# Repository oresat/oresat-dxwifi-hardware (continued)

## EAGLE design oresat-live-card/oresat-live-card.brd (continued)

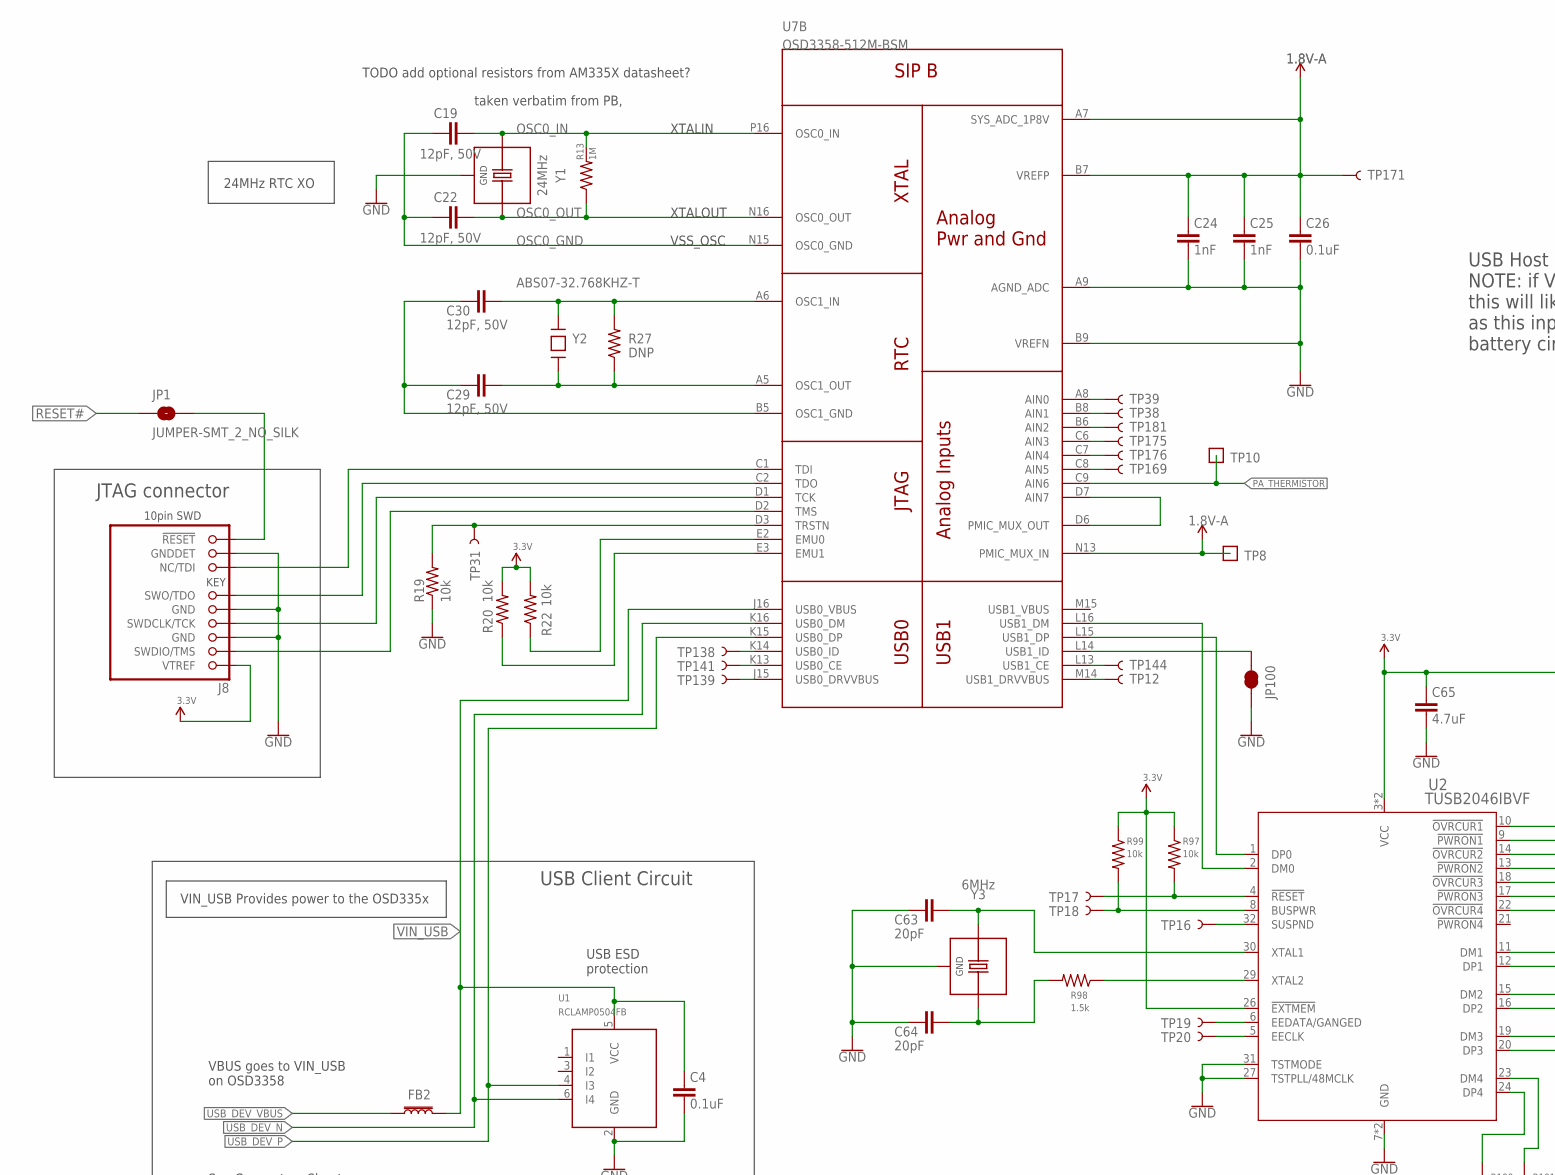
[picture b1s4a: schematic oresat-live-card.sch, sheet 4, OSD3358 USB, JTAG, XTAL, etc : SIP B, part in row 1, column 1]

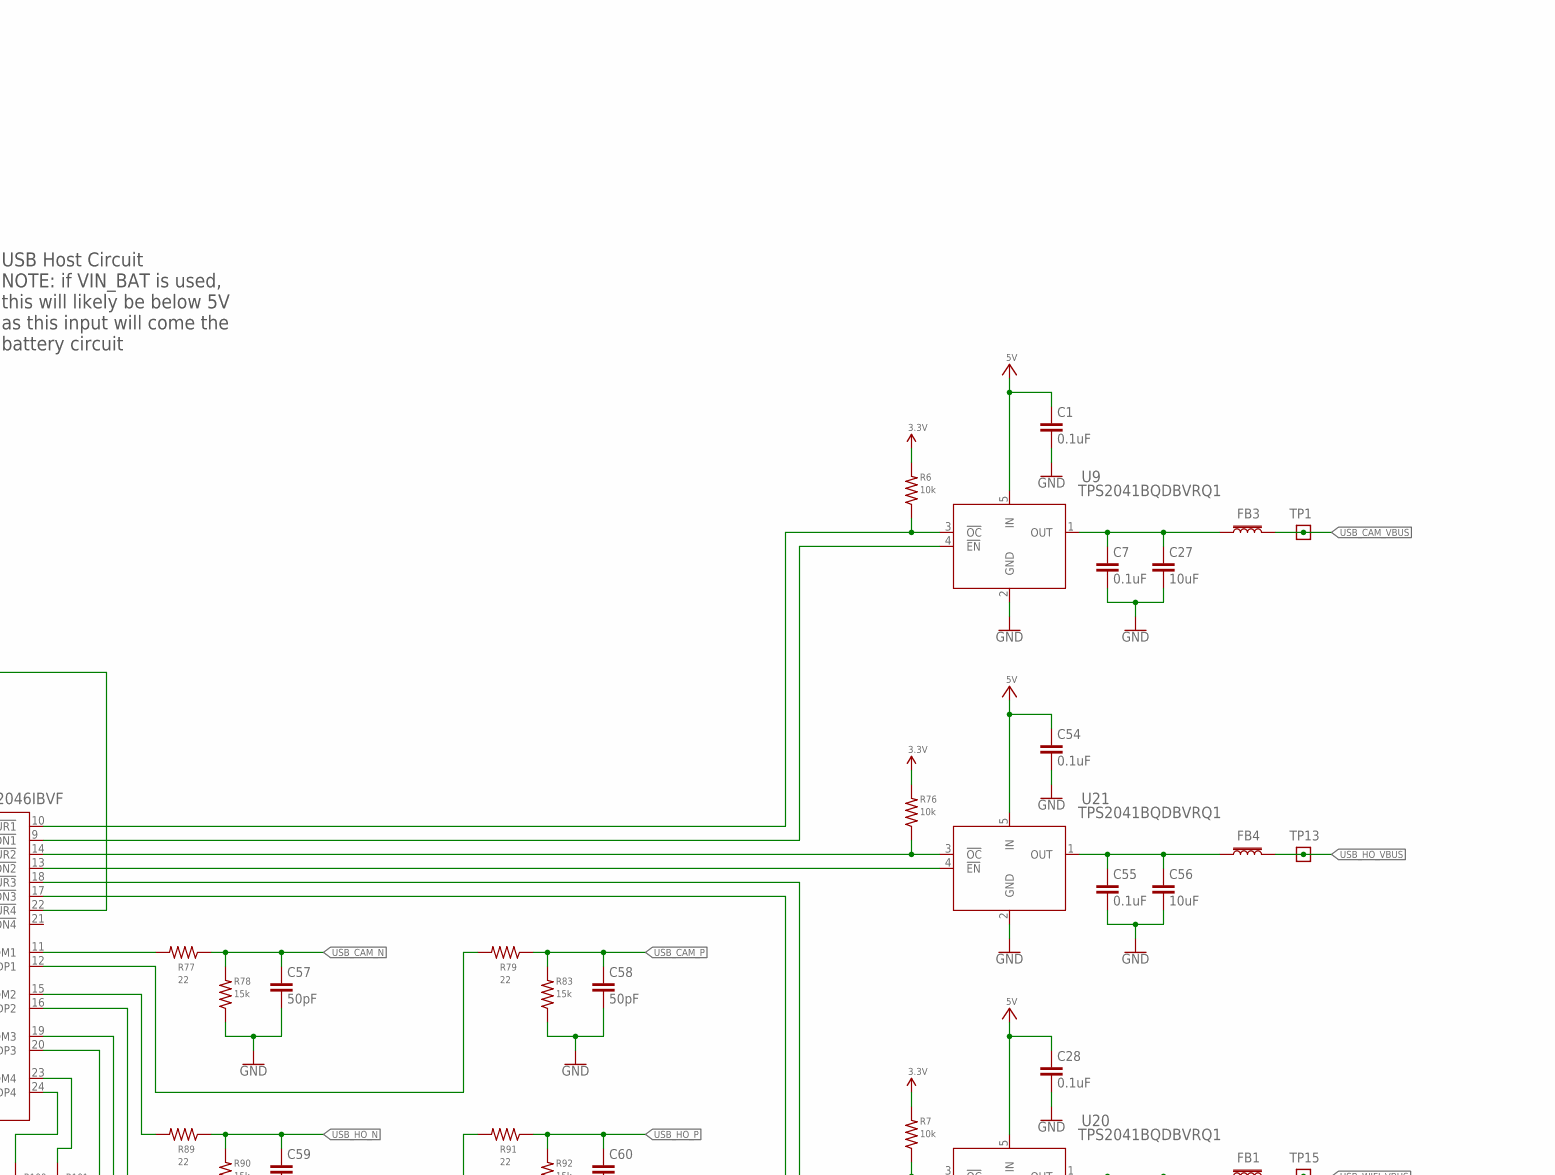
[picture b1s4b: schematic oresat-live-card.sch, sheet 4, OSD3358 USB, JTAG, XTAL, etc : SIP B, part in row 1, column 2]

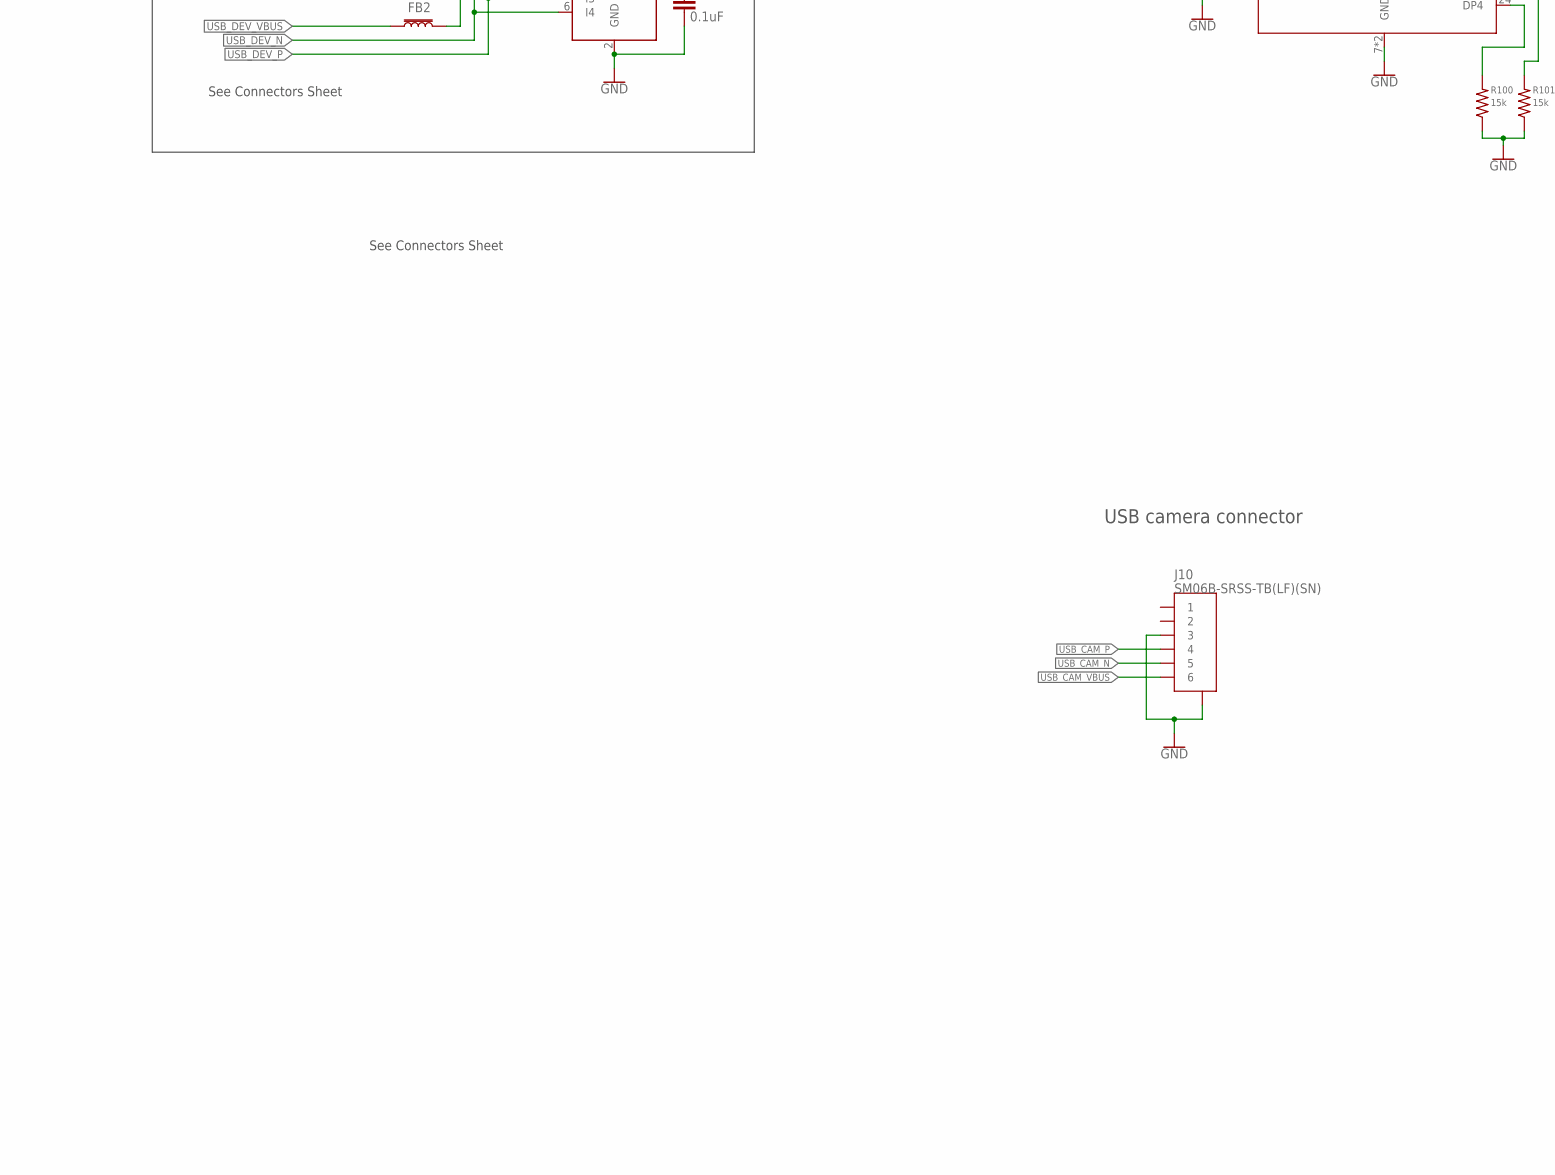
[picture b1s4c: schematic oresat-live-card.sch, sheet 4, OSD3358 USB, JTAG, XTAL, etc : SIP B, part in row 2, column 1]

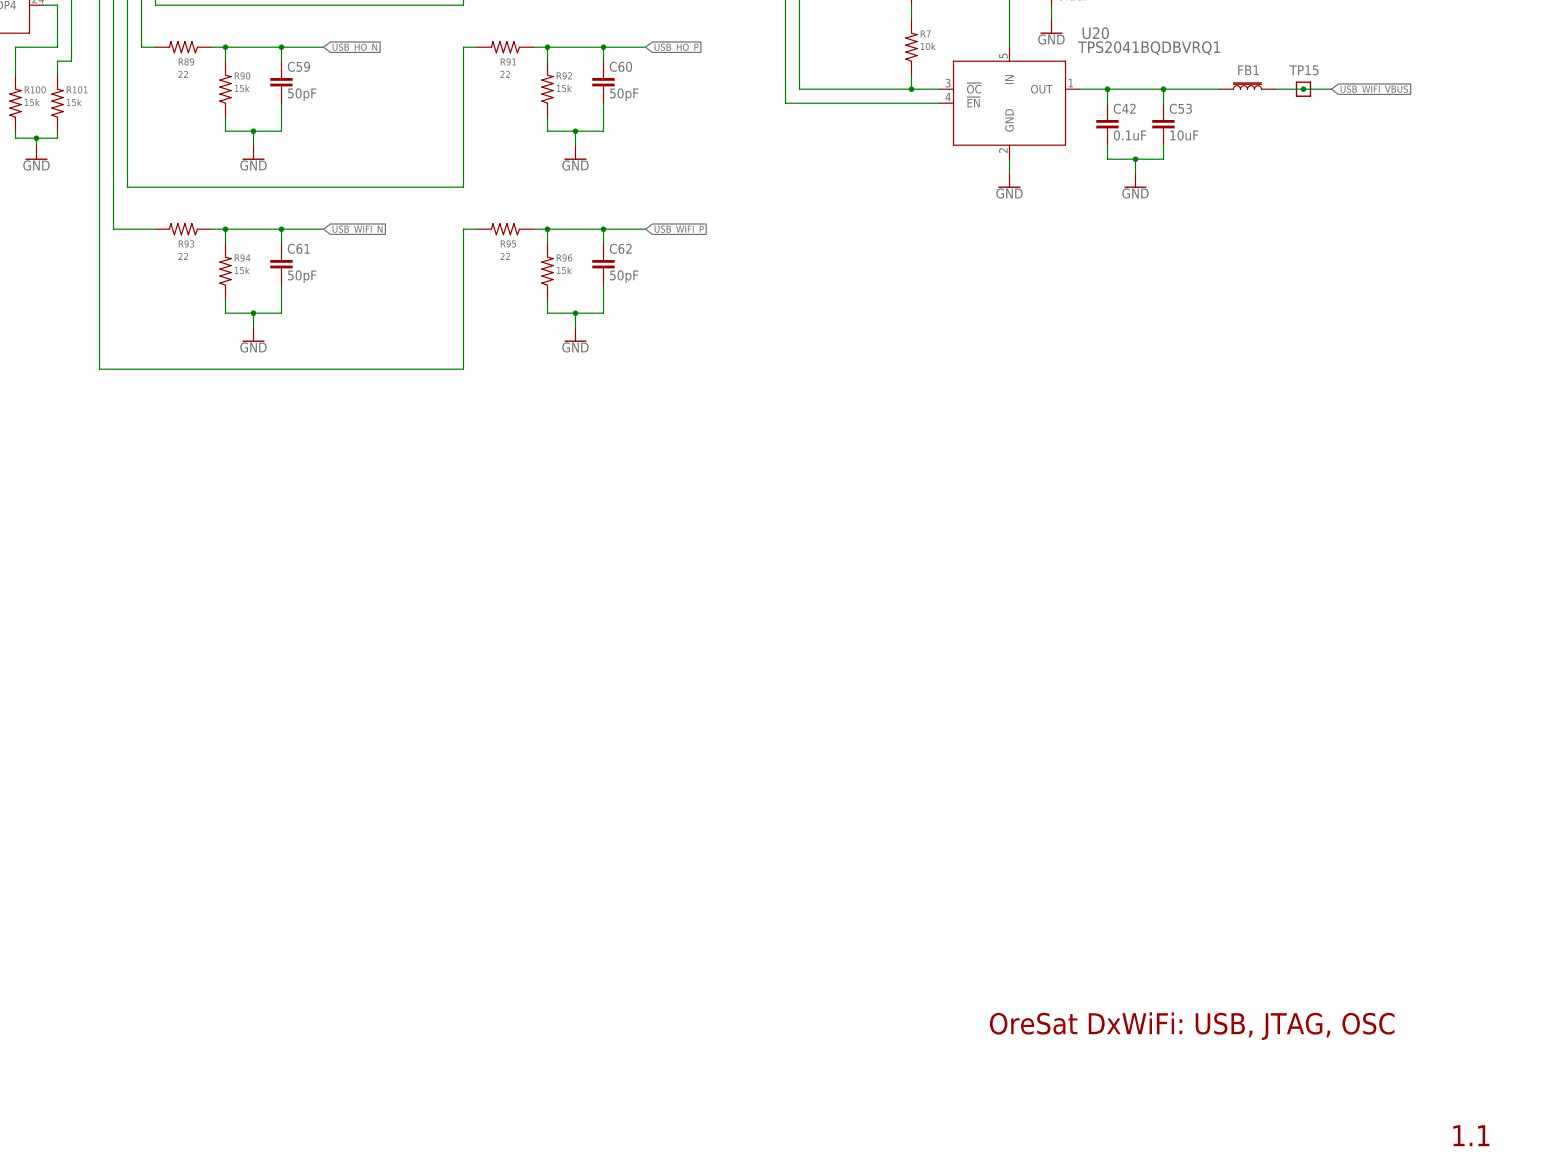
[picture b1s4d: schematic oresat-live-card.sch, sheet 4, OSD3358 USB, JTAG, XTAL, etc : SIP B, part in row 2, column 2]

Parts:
C1, C4, C7, C28, C42, C54, C55: 0.1uF; .0603-A
C19, C22, C29, C30: 12pF, 50V; .0603-A
C24, C25: 1nF; .0805-B
C26: 0.1uF; .0805-B
C27, C53, C56: 10uF; .0603-A
C57, C58, C59, C60, C61, C62: 50pF; .0603-A
C63, C64: 20pF; .0603-A
C65: 4.7uF; .0603-A
FB1, FB2, FB3, FB4: 30Ω/1.8A; 0603; MPN BLM18KG300JH1D
J8: FTSH-105-XX-X-DV-K; CON10_2X5_DUK_FTSH
J10: SM06B-SRSS-TB(LF)(SN); CONN_SM06B-SRSS-TB_JST
JP1: JUMPER-SMT_2_NO_SILK; SMT-JUMPER_2_NO_SILK
JP100: JUMPER-SMT_2_NC_TRACE_SILK; SMT-JUMPER_2_NC_TRACE_SILK
R6, R7, R19, R20, R22, R76, R97, R99: 10k; .0603-A
R13: 1M; .0603-A
R27: DNP; .0603-A
R77, R79, R89, R91, R93, R95: 22; .0603-A
R78, R83, R90, R92, R94, R96, R100, R101: 15k; .0603-A
R98: 1.5k; .0603-A
TP1, TP8, TP10, TP13, TP15: TEST-POINT; 2MM-TEST-POINT
TP12, TP16, TP17, TP18, TP19, TP20, TP31, TP38, TP39, TP138, TP139, TP141, TP144, TP169, TP171, TP175, TP176, TP181: TEST-POINT3X4; PAD.03X.04
U1: RCLAMP0504FB; SC70-6
U2: TUSB2046IBVF; QFP80P900X900X160-32N
U7: OSD3358-512M-BSM; OSD335X-BGA-256
U9, U20, U21: TPS2041BQDBVRQ1; DBV5
Y1: 24MHz; 5X3.2-4SMD
Y2: ABS07-32.768KHZ-T; CRYSTAL_3.2X1.5
Y3: 6MHz; ECS_ECS-060-18-20BM-JEN-TR

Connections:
1.8V-A: C24.1, C25.1, C26.1, TP8.1, TP171.1, U7.A7 (SYS_ADC_1P8V), U7.B7 (VREFP), U7.N13 (PMIC_MUX_IN); also elsewhere on the board
3.3V: C65.1, J8.1 (VTREF), R6.2, R7.2, R20.2, R22.2, R76.2, R97.1, R99.1, U2.3 (VCC), U2.22 (!OVRCUR4), U2.25 (VCC), U2.26 (!EXTMEM); also elsewhere on the board
5V: C1.1, C28.1, C54.1, U9.5 (IN), U20.5 (IN), U21.5 (IN); also elsewhere on the board
CAM_!OVERCUR: R6.1, U2.10 (!OVRCUR1), U9.3 (!OC)
CAM_!PWRON: U2.9 (!PWRON1), U9.4 (!EN)
GND: C1.2, C4.2, C7.2, C24.2, C25.2, C26.2, C27.2, C28.2, C42.2, C53.2, C54.2, C55.2, C56.2, C57.2, C58.2, C59.2, C60.2, C61.2, C62.2, C63.2, C64.2, C65.2, J8.3 (GND), J8.5 (GND), J8.9 (GNDDET), J10.3, J10.7, J10.8 (7), JP100.2, R19.1, R78.1, R83.1, R90.1, R92.1, R94.1, R96.1, R100.1, R101.1, U1.2 (GND), U2.7 (GND), U2.27 (TSTPLL/48MCLK), U2.28 (GND), U2.31 (TSTMODE), U7.A9 (AGND_ADC), U7.B9 (VREFN), U9.2 (GND), U20.2 (GND), U21.2 (GND), Y1.2 (GND), Y1.4 (GND), Y3.2 (GND), Y3.4 (GND); also elsewhere on the board
HO_!OVERCUR: R76.1, U2.14 (!OVRCUR2), U21.3 (!OC)
HO_!PWRON: U2.13 (!PWRON2), U21.4 (!EN)
unnamed: U7.D6 (PMIC_MUX_OUT), U7.D7 (AIN7)
unnamed: TP169.1, U7.C8 (AIN5)
unnamed: TP176.1, U7.C7 (AIN4)
unnamed: TP175.1, U7.C6 (AIN3)
unnamed: TP181.1, U7.B6 (AIN2)
unnamed: TP38.1, U7.B8 (AIN1)
unnamed: TP39.1, U7.A8 (AIN0)
unnamed: TP141.1, U7.K13 (USB0_CE)
unnamed: TP139.1, U7.J15 (USB0_DRVVBUS)
unnamed: TP12.1, U7.M14 (USB1_DRVVBUS)
unnamed: R20.1, U7.E3 (EMU1)
unnamed: TP144.1, U7.L13 (USB1_CE)
unnamed: R22.1, U7.E2 (EMU0)
unnamed: JP100.1, U7.L14 (USB1_ID)
unnamed: TP138.1, U7.K14 (USB0_ID)
unnamed: J8.10 (!RESET), JP1.2
unnamed: R100.2, U2.24 (DP4)
unnamed: C7.1, C27.1, FB3.1, U9.1 (OUT)
unnamed: TP19.1, U2.6 (EEDATA/GANGED)
unnamed: C42.1, C53.1, FB1.1, U20.1 (OUT)
unnamed: TP20.1, U2.5 (EECLK)
unnamed: C55.1, C56.1, FB4.1, U21.1 (OUT)
unnamed: R101.2, U2.23 (DM4)
unnamed: C64.1, R98.2, Y3.1 (X2)
unnamed: TP16.1, U2.32 (SUSPND)
unnamed: J8.6 (SWO/TDO), U7.C2 (TDO)
unnamed: J8.4 (SWDCLK/TCK), U7.D1 (TCK)
unnamed: J8.2 (SWDIO/TMS), U7.D2 (TMS)
unnamed: J8.8 (NC/TDI), U7.C1 (TDI)
unnamed: R19.2, TP31.1, U7.D3 (TRSTN)
OSC0_GND: C19.1, C22.1, U7.N15 (OSC0_GND)
OSC0_IN: C19.2, R13.2, U7.P16 (OSC0_IN), Y1.1 (X1)
OSC0_OUT: C22.2, R13.1, U7.N16 (OSC0_OUT), Y1.3 (X2)
OSC1_GND1: C29.2, C30.2, U7.B5 (OSC1_GND)
OSC1_IN1: C30.1, R27.2, U7.A6 (OSC1_IN), Y2.P$2
OSC1_OUT1: C29.1, R27.1, U7.A5 (OSC1_OUT), Y2.P$1
PA_THERMISTOR: TP10.1, U7.C9 (AIN6); also elsewhere on the board
RESET#: JP1.1; also elsewhere on the board
TUSB_!RESET: R97.2, TP17.1, U2.4 (!RESET)
TUSB_BUSPWR: R99.2, TP18.1, U2.8 (BUSPWR)
TUSB_XTAL1: C63.1, U2.30 (XTAL1), Y3.3 (X1)
TUSB_XTAL2: R98.1, U2.29 (XTAL2)
USB1_N: U2.2 (DM0), U7.L16 (USB1_DM)
USB1_P: U2.1 (DP0), U7.L15 (USB1_DP)
USBH1_N: R77.2, U2.11 (DM1)
USBH1_P: R79.2, U2.12 (DP1)
USBH2_N: R89.2, U2.15 (DM2)
USBH2_P: R91.2, U2.16 (DP2)
USBH3_N: R93.2, U2.19 (DM3)
USBH3_P: R95.2, U2.20 (DP3)
USB_CAM_N: C57.1, J10.5, R77.1, R78.2
USB_CAM_P: C58.1, J10.4, R79.1, R83.2
USB_CAM_VBUS: FB3.2, J10.6, TP1.1
USB_DEV_N: U1.6 (I4), U7.K16 (USB0_DM); also elsewhere on the board
USB_DEV_P: U1.4 (I3), U7.K15 (USB0_DP); also elsewhere on the board
USB_DEV_VBUS: FB2.1; also elsewhere on the board
USB_HO_N: C59.1, R89.1, R90.2; also elsewhere on the board
USB_HO_P: C60.1, R91.1, R92.2; also elsewhere on the board
USB_HO_VBUS: FB4.2, TP13.1; also elsewhere on the board
USB_WIFI_N: C61.1, R93.1, R94.2; also elsewhere on the board
USB_WIFI_P: C62.1, R95.1, R96.2; also elsewhere on the board
USB_WIFI_VBUS: FB1.2, TP15.1; also elsewhere on the board
VIN_USB: C4.1, FB2.2, U1.5 (VCC), U7.J16 (USB0_VBUS); also elsewhere on the board
WIFI_!OVERCUR: R7.1, U2.18 (!OVRCUR3), U20.3 (!OC)
WIFI_!PWRON: U2.17 (!PWRON3), U20.4 (!EN)

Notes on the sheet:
taken verbatim from PB,
VBUS goes to VIN_USB on OSD3358
USB ESD protection
USB Host Circuit NOTE: if VIN_BAT is used, this will likely be below 5V as this input will come the battery circuit
JTAG connector
USB Client Circuit
24MHz RTC XO
See Connectors Sheet
TODO add optional resistors from AM335X datasheet?
XTALIN
XTALOUT
VSS_OSC
VIN_USB Provides power to the OSD335x
OreSat DxWiFi: USB, JTAG, OSC
1.1
USB camera connector

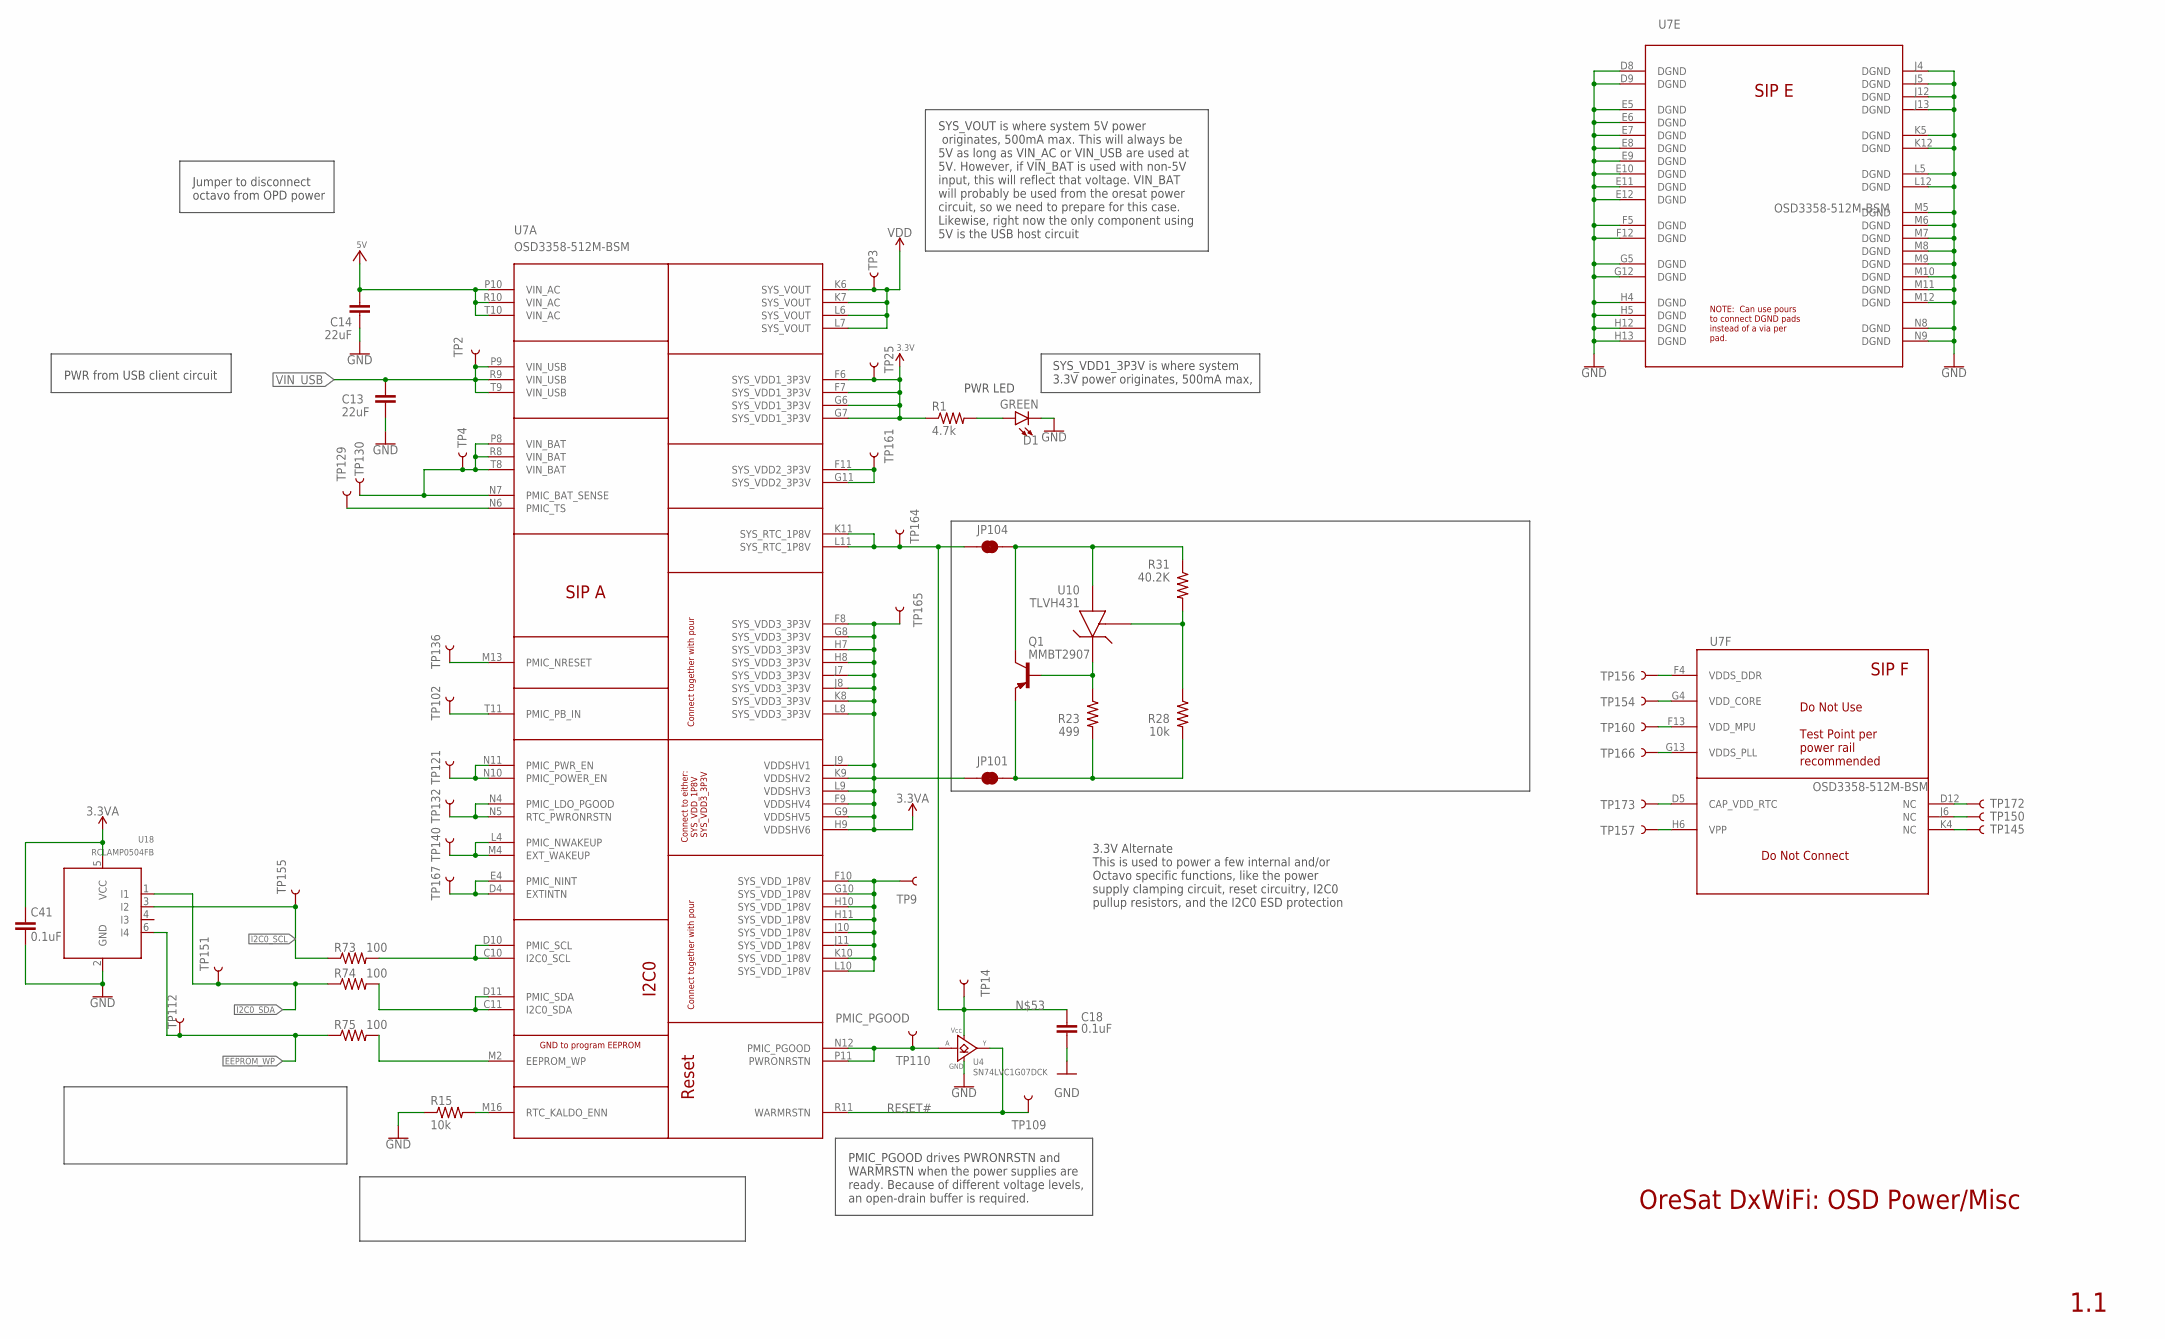
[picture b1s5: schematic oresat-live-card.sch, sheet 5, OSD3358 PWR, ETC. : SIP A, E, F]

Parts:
C13, C14: 22uF; C1210
C18, C41: 0.1uF; .0603-A
D1: GREEN; LED-0603; MANUFACTURER_PART_NUMBER 150060VS55040; DIGI-KEY_PART_NUMBER 732-12017-1-ND
JP101, JP104: JUMPER-SMT_2_NC_TRACE_SILK; SMT-JUMPER_2_NC_TRACE_SILK
Q1: MMBT2907; SOT23-BEC
R1: 4.7k; .0603-A
R15, R28: 10k; .0603-A
R23: 499; .0603-A
R31: 40.2K; .0603-A
R73, R74, R75: 100; .0603-A
TP2, TP3, TP4, TP9, TP14, TP25, TP102, TP109, TP110, TP112, TP121, TP129, TP130, TP132, TP136, TP140, TP145, TP150, TP151, TP154, TP155, TP156, TP157, TP160, TP161, TP164, TP165, TP166, TP167, TP172, TP173: TEST-POINT3X4; PAD.03X.04
U4: SN74LVC1G07DCK; C70(TI-DCK)
U7: OSD3358-512M-BSM; OSD335X-BGA-256
U10: TLVH431; SOT23-3
U18: RCLAMP0504FB; SC70-6

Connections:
3.3V: R1.1, TP25.1, U7.F6 (SYS_VDD1_3P3V), U7.F7 (SYS_VDD1_3P3V), U7.G6 (SYS_VDD1_3P3V), U7.G7 (SYS_VDD1_3P3V); also elsewhere on the board
3.3VA: C41.1, JP101.1, TP165.1, U7.F8 (SYS_VDD3_3P3V), U7.F9 (VDDSHV4), U7.G8 (SYS_VDD3_3P3V), U7.G9 (VDDSHV5), U7.H7 (SYS_VDD3_3P3V), U7.H8 (SYS_VDD3_3P3V), U7.H9 (VDDSHV6), U7.J7 (SYS_VDD3_3P3V), U7.J8 (SYS_VDD3_3P3V), U7.J9 (VDDSHV1), U7.K8 (SYS_VDD3_3P3V), U7.K9 (VDDSHV2), U7.L8 (SYS_VDD3_3P3V), U7.L9 (VDDSHV3), U18.5 (VCC)
5V: C14.1, U7.P10 (VIN_AC), U7.R10 (VIN_AC), U7.T10 (VIN_AC); also elsewhere on the board
EEPROM_WP: R75.1, TP112.1, U18.6 (I4); also elsewhere on the board
GND: C13.2, C14.2, C18.2, C41.2, D1.C, R15.1, U4.3 (GND), U7.D8 (DGND), U7.D9 (DGND), U7.E5 (DGND), U7.E6 (DGND), U7.E7 (DGND), U7.E8 (DGND), U7.E9 (DGND), U7.E10 (DGND), U7.E11 (DGND), U7.E12 (DGND), U7.F5 (DGND), U7.F12 (DGND), U7.G5 (DGND), U7.G12 (DGND), U7.H4 (DGND), U7.H5 (DGND), U7.H12 (DGND), U7.H13 (DGND), U7.J4 (DGND), U7.J5 (DGND), U7.J12 (DGND), U7.J13 (DGND), U7.K5 (DGND), U7.K12 (DGND), U7.L5 (DGND), U7.L12 (DGND), U7.M5 (DGND), U7.M6 (DGND), U7.M7 (DGND), U7.M8 (DGND), U7.M9 (DGND), U7.M10 (DGND), U7.M11 (DGND), U7.M12 (DGND), U7.N8 (DGND), U7.N9 (DGND), U18.2 (GND); also elsewhere on the board
I2C0_SCL: R73.1, TP155.1, U18.3 (I2); also elsewhere on the board
I2C0_SDA: R74.1, TP151.1, U18.1 (I1); also elsewhere on the board
unnamed: TP9.1, U7.F10 (SYS_VDD_1P8V), U7.G10 (SYS_VDD_1P8V), U7.H10 (SYS_VDD_1P8V), U7.H11 (SYS_VDD_1P8V), U7.J10 (SYS_VDD_1P8V), U7.J11 (SYS_VDD_1P8V), U7.K10 (SYS_VDD_1P8V), U7.L10 (SYS_VDD_1P8V)
unnamed: JP101.2, Q1.E, R23.2, R28.2
unnamed: R28.1, R31.2, U10.1 (REF)
unnamed: Q1.B, R23.1, U10.2 (CATHODE)
unnamed: C18.1, JP104.1, TP14.1, TP164.1, U4.5 (VCC), U7.K11 (SYS_RTC_1P8V), U7.L11 (SYS_RTC_1P8V)
unnamed: TP172.1, U7.D12 (NC)
unnamed: TP150.1, U7.J6 (NC)
unnamed: TP145.1, U7.K4 (NC)
unnamed: TP157.1, U7.H6 (VPP)
unnamed: TP173.1, U7.D5 (CAP_VDD_RTC)
unnamed: TP166.1, U7.G13 (VDDS_PLL)
unnamed: TP160.1, U7.F13 (VDD_MPU)
unnamed: TP154.1, U7.G4 (VDD_CORE)
unnamed: TP156.1, U7.F4 (VDDS_DDR)
unnamed: D1.A, R1.2
unnamed: R74.2, U7.C11 (I2C0_SDA), U7.D11 (PMIC_SDA)
unnamed: R75.2, U7.M2 (EEPROM_WP)
unnamed: R73.2, U7.C10 (I2C0_SCL), U7.D10 (PMIC_SCL)
unnamed: TP4.1, TP130.1, U7.N7 (PMIC_BAT_SENSE), U7.P8 (VIN_BAT), U7.R8 (VIN_BAT), U7.T8 (VIN_BAT)
unnamed: TP129.1, U7.N6 (PMIC_TS)
unnamed: TP161.1, U7.F11 (SYS_VDD2_3P3V), U7.G11 (SYS_VDD2_3P3V)
unnamed: JP104.2, Q1.C, R31.1, U10.3 (ANODE)
unnamed: TP167.1, U7.D4 (EXTINTN), U7.E4 (PMIC_NINT)
unnamed: TP140.1, U7.L4 (PMIC_NWAKEUP), U7.M4 (EXT_WAKEUP)
unnamed: TP132.1, U7.N4 (PMIC_LDO_PGOOD), U7.N5 (RTC_PWRONRSTN)
unnamed: TP121.1, U7.N10 (PMIC_POWER_EN), U7.N11 (PMIC_PWR_EN)
unnamed: TP102.1, U7.T11 (PMIC_PB_IN)
unnamed: TP136.1, U7.M13 (PMIC_NRESET)
unnamed: R15.2, U7.M16 (RTC_KALDO_ENN)
PMIC_PGOOD: TP110.1, U4.2 (A), U7.N12 (PMIC_PGOOD), U7.P11 (PWRONRSTN)
RESET#: TP109.1, U4.4 (Y), U7.R11 (WARMRSTN); also elsewhere on the board
VDD: TP3.1, U7.K6 (SYS_VOUT), U7.K7 (SYS_VOUT), U7.L6 (SYS_VOUT), U7.L7 (SYS_VOUT)
VIN_USB: C13.1, TP2.1, U7.P9 (VIN_USB), U7.R9 (VIN_USB), U7.T9 (VIN_USB); also elsewhere on the board

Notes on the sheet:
SYS_VOUT is where system 5V power originates, 500mA max. This will always be 5V as long as VIN_AC or VIN_USB are used at 5V. However, if VIN_BAT is used with non-5V input, this will reflect that voltage. VIN_BAT will probably be used from the oresat power circuit, so we need to prepare for this cas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
SYS_VDD1_3P3V is where system 3.3V power originates, 500mA max,
PWR LED
PMIC_PGOOD drives PWRONRSTN and WARMRSTN when the power supplies are ready. Because of different voltage levels, an open-drain buffer is required.
PWR from USB client circuit
Jumper to disconnect octavo from OPD power
3.3V Alternate This is used to power a few internal and/or Octavo specific functions, like the power supply clamping circuit, reset circuitry, I2C0 pullup resistors, and the I2C0 ESD protection
OreSat DxWiFi: OSD Power/Misc
1.1

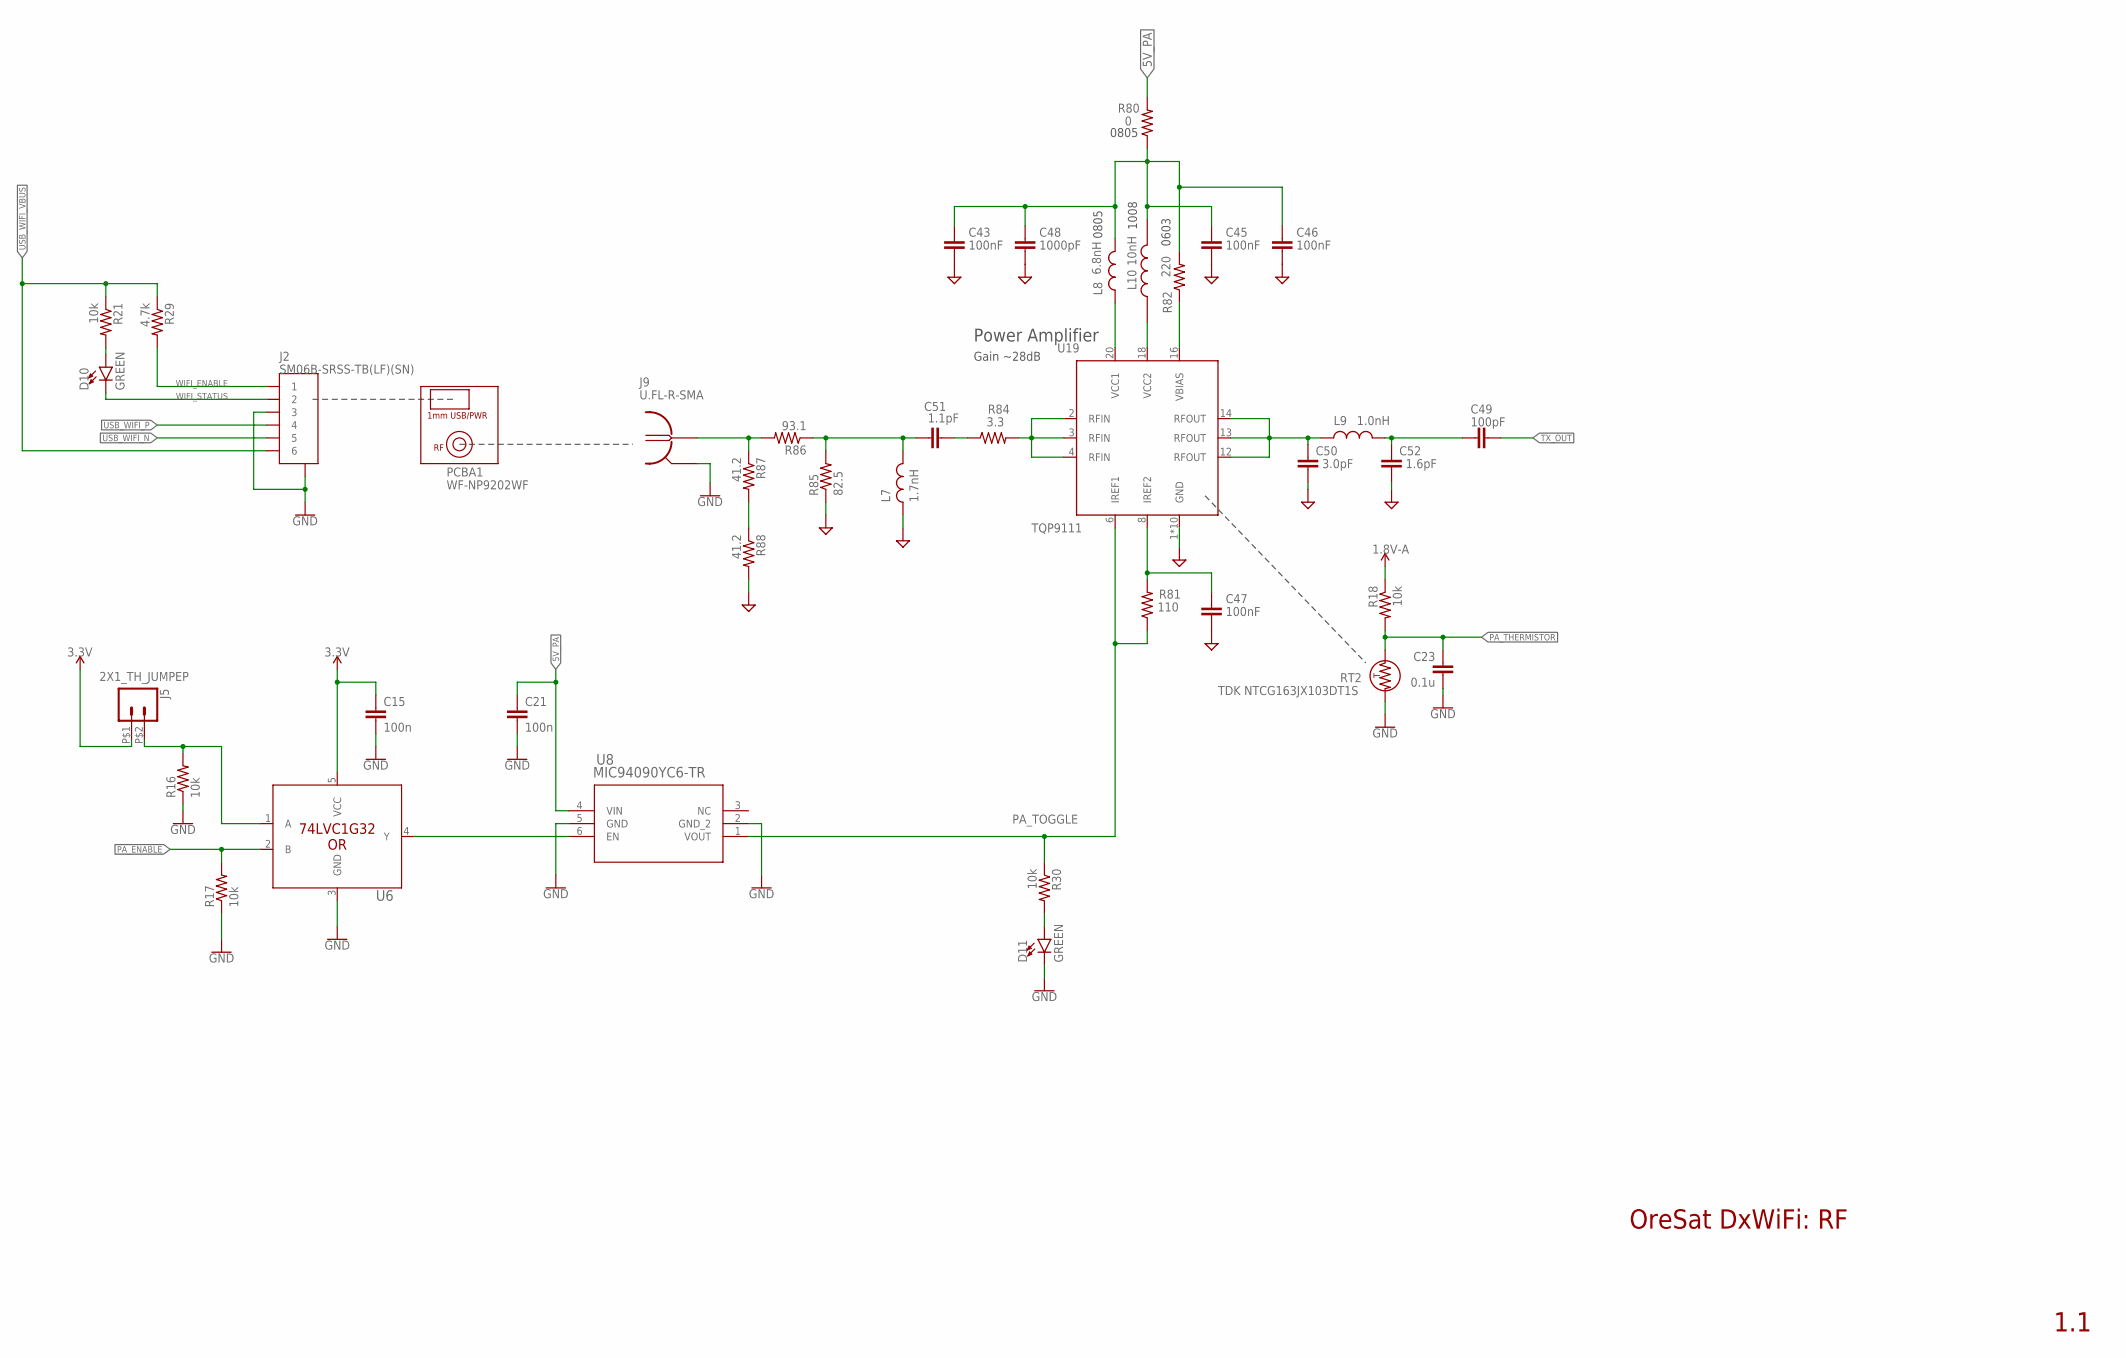
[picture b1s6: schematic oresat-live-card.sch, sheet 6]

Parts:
C15, C21: 100n; .0603-A
C23: 0.1u; .0603-A
C43, C45, C46: 100nF; .0402-B-NOSILK; MPN CGA2B1X7R1C104K050BC
C47: 100nF; .0402-C-NOSILK; MPN CGA2B1X7R1C104K050BC
C48: 1000pF; .0402-B-NOSILK; MPN CGA2B2NP01H102J050BA
C49: 100pF; .0402-C-NOSILK; MPN GCM1885C1H101JA16D
C50: 3.0pF; .0402-C-NOSILK; MPN 04025U3R0BAT2A
C51: 1.1pF; .0402-C-NOSILK; MPN 04025J1R1PBSTR\500
C52: 1.6pF; .0402-C-NOSILK; MPN 04025U1R6BAT2A
D10, D11: GREEN; LED-0603; MANUFACTURER_PART_NUMBER 150060VS55040; DIGI-KEY_PART_NUMBER 732-12017-1-ND
J2: SM06B-SRSS-TB(LF)(SN); CONN_SM06B-SRSS-TB_JST
J5: 2X1_TH_JUMPEP; 2X1
J9: U.FL-R-SMA; U.FL-R-SMT
L7: 1.7nH; .0402-C-NOSILK; MPN 0402DC-1N7XJRU
L8: 6.8nH; .0805-C-NOSILK; MPN 0805CS-060XJLC
L9: 1.0nH; .0402-C-NOSILK; MPN MLK1005S1N0ST000
L10: 10nH; INDC2928X203N
PCBA1: WF-NP9202WF; WF-NP9202
R16, R17, R18, R21, R30: 10k; .0603-A
R29: 4.7k; .0603-A
R80: 0; R0805; MPN ERJ-6GEY0R00V
R81: 110; .0402-B-NOSILK; MPN ERJ-2RKF1100X
R82: 220; .0603-C-NOSILK; MPN ERJ-3EKF2200V
R84: 3.3; .0402-C-NOSILK; MPN CRCW04023R30FKED
R85: 82.5; .0603-A; MPN ERJ-3EKF82R5V
R86: 93.1; .0603-A; MPN ERJ-3EKF93R1V
R87, R88: 41.2; .0603-A; MPN ERJ-3EKF41R2V
RT2: TDK NTCG163JX103DT1S; 0603-THERMISTOR-B
U6: SN74LVC1G32QDBVRQ1; DBV5
U8: MIC94090YC6-TR; SC-70-6_MCH
U19: TQP9111; QFN50P400X400X102-21N

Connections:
1.8V-A: R18.1; also elsewhere on the board
3.3V: C15.1, J5.P$1 (1), U6.5 (VCC); also elsewhere on the board
5V_PA: C21.1, R80.2, U8.4 (VIN); also elsewhere on the board
GND: C15.2, C21.2, C23.2, C43.2, C45.2, C46.2, C47.2, C48.2, C50.2, C52.2, D11.C, J2.3, J2.7, J2.8 (7), J9.2, J9.3, L7.1, R16.1, R17.1, R85.1, R88.2, RT2.2, U6.3 (GND), U8.2 (GND_2), U8.5 (GND), U19.1 (GND), U19.5 (GND), U19.7 (GND), U19.9 (GND), U19.10 (GND), U19.11 (GND), U19.15 (GND), U19.17 (GND), U19.19 (GND), U19.21 (GND); also elsewhere on the board
unnamed: D10.A, R21.2
unnamed: D11.A, R30.2
unnamed: J5.P$2 (2), R16.2, U6.1 (A)
unnamed: U6.4 (Y), U8.6 (EN)
unnamed: C43.1, C45.1, C46.1, C48.1, L8.2, L10.2, R80.1, R82.2
unnamed: C47.1, R81.2, U19.8 (IREF2)
unnamed: C50.1, L9.1, U19.12 (RFOUT), U19.13 (RFOUT), U19.14 (RFOUT)
unnamed: C49.1, C52.1, L9.2
unnamed: R84.2, U19.2 (RFIN), U19.3 (RFIN), U19.4 (RFIN)
unnamed: R82.1, U19.16 (VBIAS)
unnamed: L8.1, U19.20 (VCC1)
unnamed: L10.1, U19.18 (VCC2)
unnamed: C51.2, R84.1
unnamed: R87.2, R88.1
unnamed: C51.1, L7.2, R85.2, R86.1
PA_ENABLE: R17.2, U6.2 (B); also elsewhere on the board
PA_THERMISTOR: C23.1, R18.2, RT2.1; also elsewhere on the board
PA_TOGGLE: R30.1, R81.1, U8.1 (VOUT), U19.6 (IREF1)
TX_IN: J9.1, R86.2, R87.1
TX_OUT: C49.2; also elsewhere on the board
USB_WIFI_N: J2.5; also elsewhere on the board
USB_WIFI_P: J2.4; also elsewhere on the board
USB_WIFI_VBUS: J2.6, R21.1, R29.1; also elsewhere on the board
WIFI_ENABLE: J2.1, R29.2
WIFI_STATUS: D10.C, J2.2

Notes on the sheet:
OreSat DxWiFi: RF
1.1
0805
0603
Power Amplifier
Gain ~28dB
1008
